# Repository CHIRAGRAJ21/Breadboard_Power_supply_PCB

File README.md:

This PCB is a component of a breadboard power supply. It could be used to provide power to circuits implemented on a mini breadboard, which is a core part of electronics prototyping.
This breadboard power supply has following features:
  1. Plugs directly on the breadboard; therefore, there are no wires.
  2. Has an on/off switch.
  3. Can provide 5V and 3.3V power.
  4. Can draw power from a range of wall power supplies, from 6V to 12V.
The connection between the breadboard and the PCB is made via two sets of pin headers.
Also, I have added two double screw terminals to provide an additional way to output power via jumper wires instead of the pins.

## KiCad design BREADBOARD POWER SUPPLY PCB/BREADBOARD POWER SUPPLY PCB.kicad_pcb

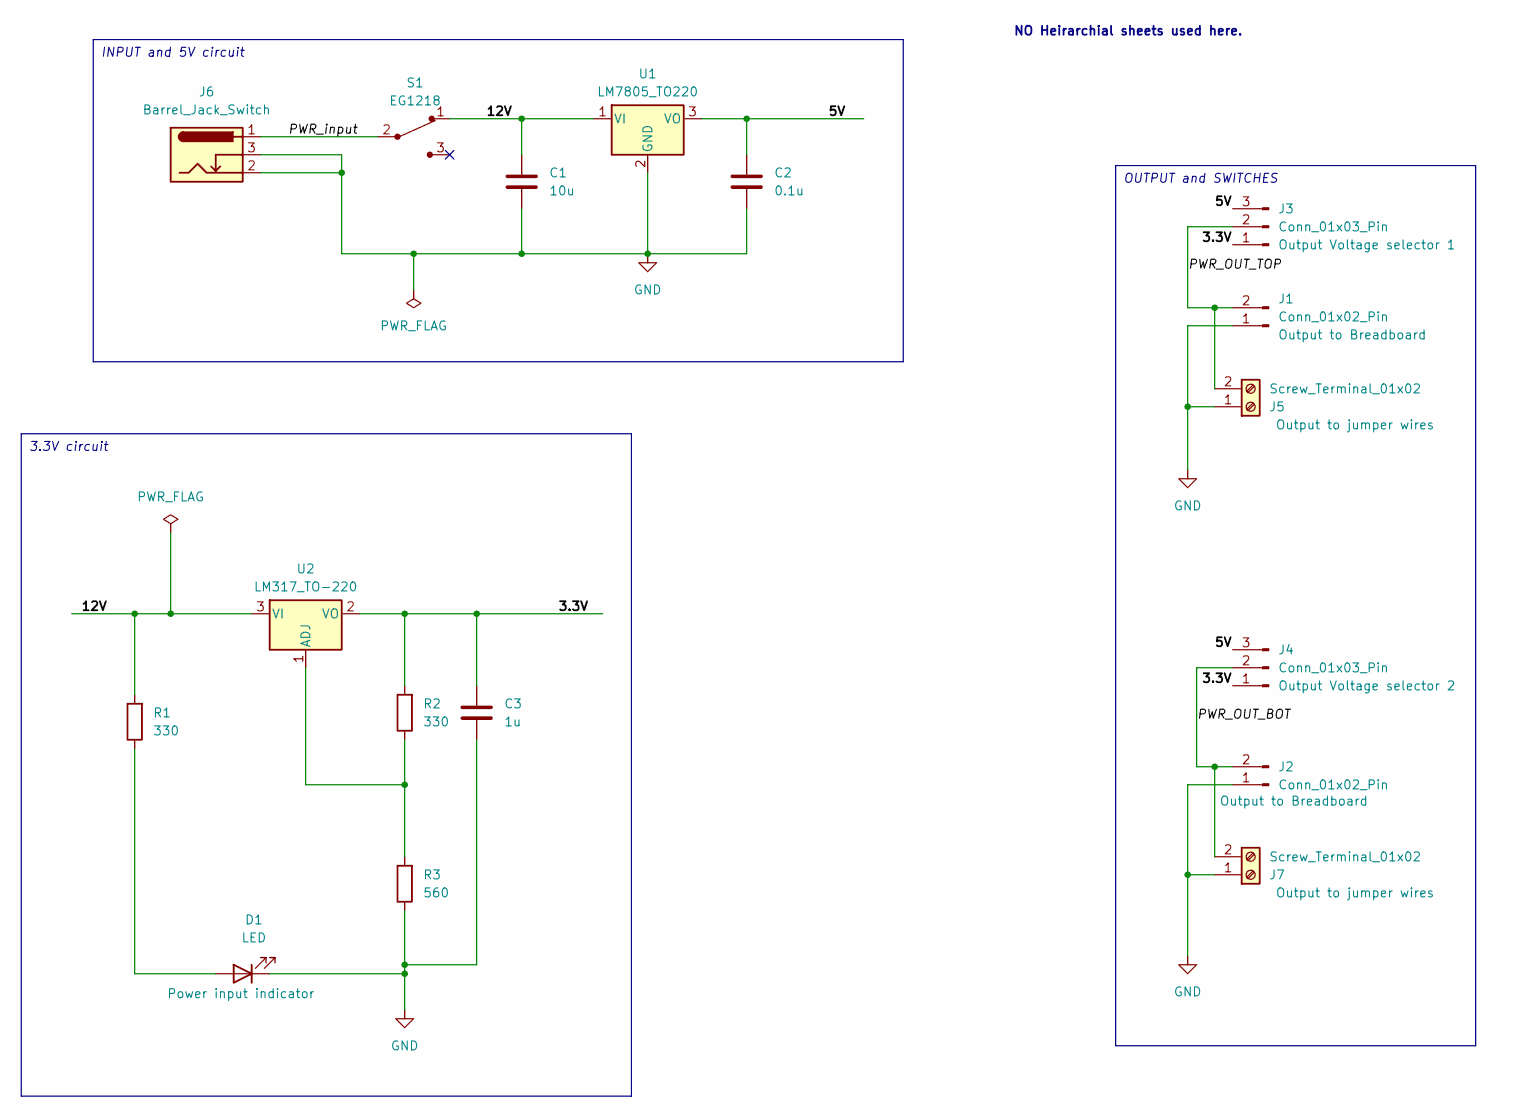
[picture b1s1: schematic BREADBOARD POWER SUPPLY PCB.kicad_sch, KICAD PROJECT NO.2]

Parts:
C1: 10u; C_Disc_D3.0mm_W1.6mm_P2.50mm
C2: 0.1u; C_Disc_D3.0mm_W1.6mm_P2.50mm
C3: 1u; C_Disc_D3.0mm_W1.6mm_P2.50mm
D1: LED; LED_D5.0mm
J1, J2: Conn_01x02_Pin; PinHeader_1x02_P2.54mm_Vertical
J3, J4: Conn_01x03_Pin; PinHeader_1x03_P2.54mm_Vertical
J5, J7: Screw_Terminal_01x02; TerminalBlock_bornier-2_P5.08mm
J6: Barrel_Jack_Switch; BarrelJack_Horizontal
R1, R2: 330; R_Axial_DIN0204_L3.6mm_D1.6mm_P7.62mm_Horizontal
R3: 560; R_Axial_DIN0204_L3.6mm_D1.6mm_P7.62mm_Horizontal
S1: EG1218; Switch_Slide_11.6x4mm_EG1218; MPN EG1218
U1: LM7805_TO220; TO-220-3_Vertical
U2: LM317_TO-220; TO-220-3_Vertical

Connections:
/3.3V: C3.1, J3.1, J4.1, R2.2, U2.2 (VO)
/5V: C2.1, J3.3, J4.3, U1.3 (VO)
/12V: C1.1, R1.2, S1.1, U1.1 (VI), U2.3 (VI)
/PWR_OUT_BOT: J2.2, J4.2, J7.2
/PWR_OUT_TOP: J1.2, J3.2, J5.2
/PWR_input: J6.1, S1.2
GND: C1.2, C2.2, C3.2, D1.1 (K), J1.1, J2.1, J5.1, J6.2, J6.3, J7.1, R3.1, U1.2 (GND)
unnamed: D1.2 (A), R1.1
unnamed: R2.1, R3.2, U2.1 (ADJ)

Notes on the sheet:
INPUT and 5V circuit
3.3V circuit
OUTPUT and SWITCHES
NO Heirarchial sheets used here.

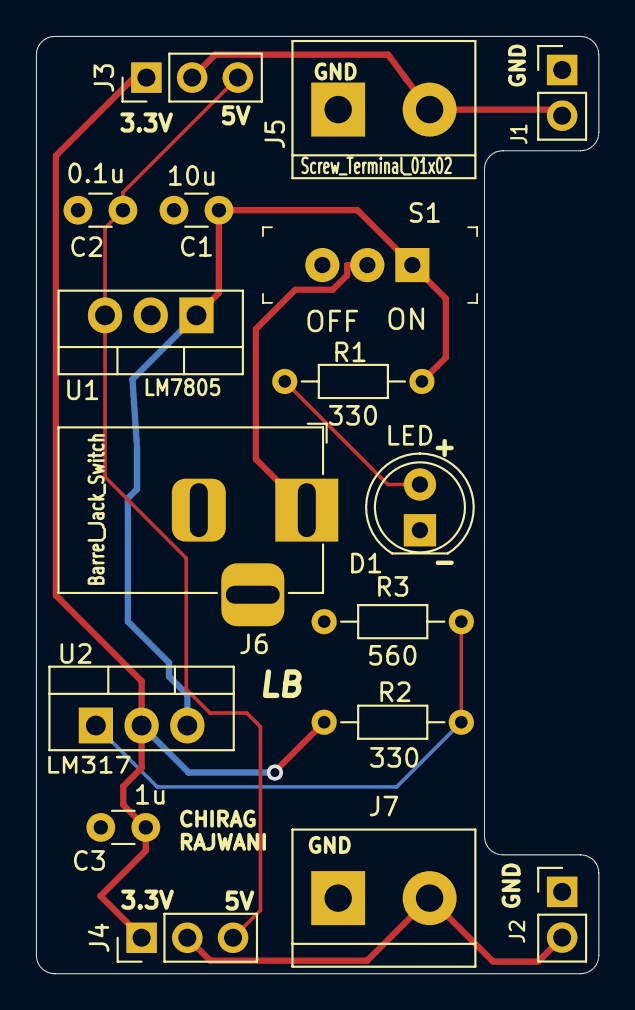
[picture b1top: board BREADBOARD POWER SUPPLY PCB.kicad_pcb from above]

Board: 2 copper layers, 31.2 x 52.1 mm, 17 parts (0 on the bottom side), 9 nets.

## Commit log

2024-06-30 First commit.
2024-06-30 This is a 2-layer PCB mechanical and dimensional constrained project.
2024-06-30 Today is SUNDAY.
2024-06-30 Added a capacitor and updated gitignore.
2024-06-30 Deleted the capcitnce from main branch.
2024-06-30 No major changes required in schematic and PCB new layout.
2024-06-30 Thermal relief connections related errors occured when connection to pads type was chosen as 'Thermal Releif' during the experimentation with laying out hatch pattern based copper filled zones.
2024-12-20 Created README.md
2024-12-20 Added Gerber files
    For proper analysis and view of each of the layers of the double sided Pcb
